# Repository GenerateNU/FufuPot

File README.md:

# Fufu Pot
TODO: Add Blurb

## Directory Structure:
```
.
|
|───production  # contains files needed for final prototype
|   |
|   |───fufpot-eCAD    # contains the KiCAD project
|   └───fufupot-src     # contains the code needed for deployment
|
|───testing     # contains files relevant to testing components
|
└───README.md   # this file!
```

## Practice Good Git Hygiene!
1. Only commit files you intended to change
2. Create branches for each feature, and larger branches for each development effort (i.e. ```develop/*```)
3. Check your branch before starting work
4. Pull frequently to avoid conflicts
5. Make Pull Requests when you are ready to merge into a larger branch

## Git Resources

* [Setting up Git](https://fanatical-colossus-434.notion.site/Git-Installation-and-Setup-d07b7d1ab5544424876f9fd3b4a0b312)
* [Intro to Git Crash Course](https://fanatical-colossus-434.notion.site/Crash-Course-Intro-to-Git-809641611da9478b8f9cca8fd97e49fe)

## EE Resources

* [Intro to KiCAD](https://fanatical-colossus-434.notion.site/EE-Crashcourse-Using-Kicad-To-Design-Schematics-8c7091b07237425bae66616ad1f77371)
* [EE Crash Course](https://fanatical-colossus-434.notion.site/EE-Crash-Course-Hardware-2023-c0c7cd5b55cf401e87f8b6c2c8c84336)

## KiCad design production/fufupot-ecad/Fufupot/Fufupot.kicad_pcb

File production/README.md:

# Production
This directory is for code/schematics/layouts that will be implemented in the final prototype.

> **_NOTE:_** If you have code to test out a component/subsystem, it should probably go into ```/testing```

## Directory Structure:
```
.
|───fufupot-ecad    # contains any schematic/board development files
|
└───fufupot-src     # contains any embedded code or important scripts
```

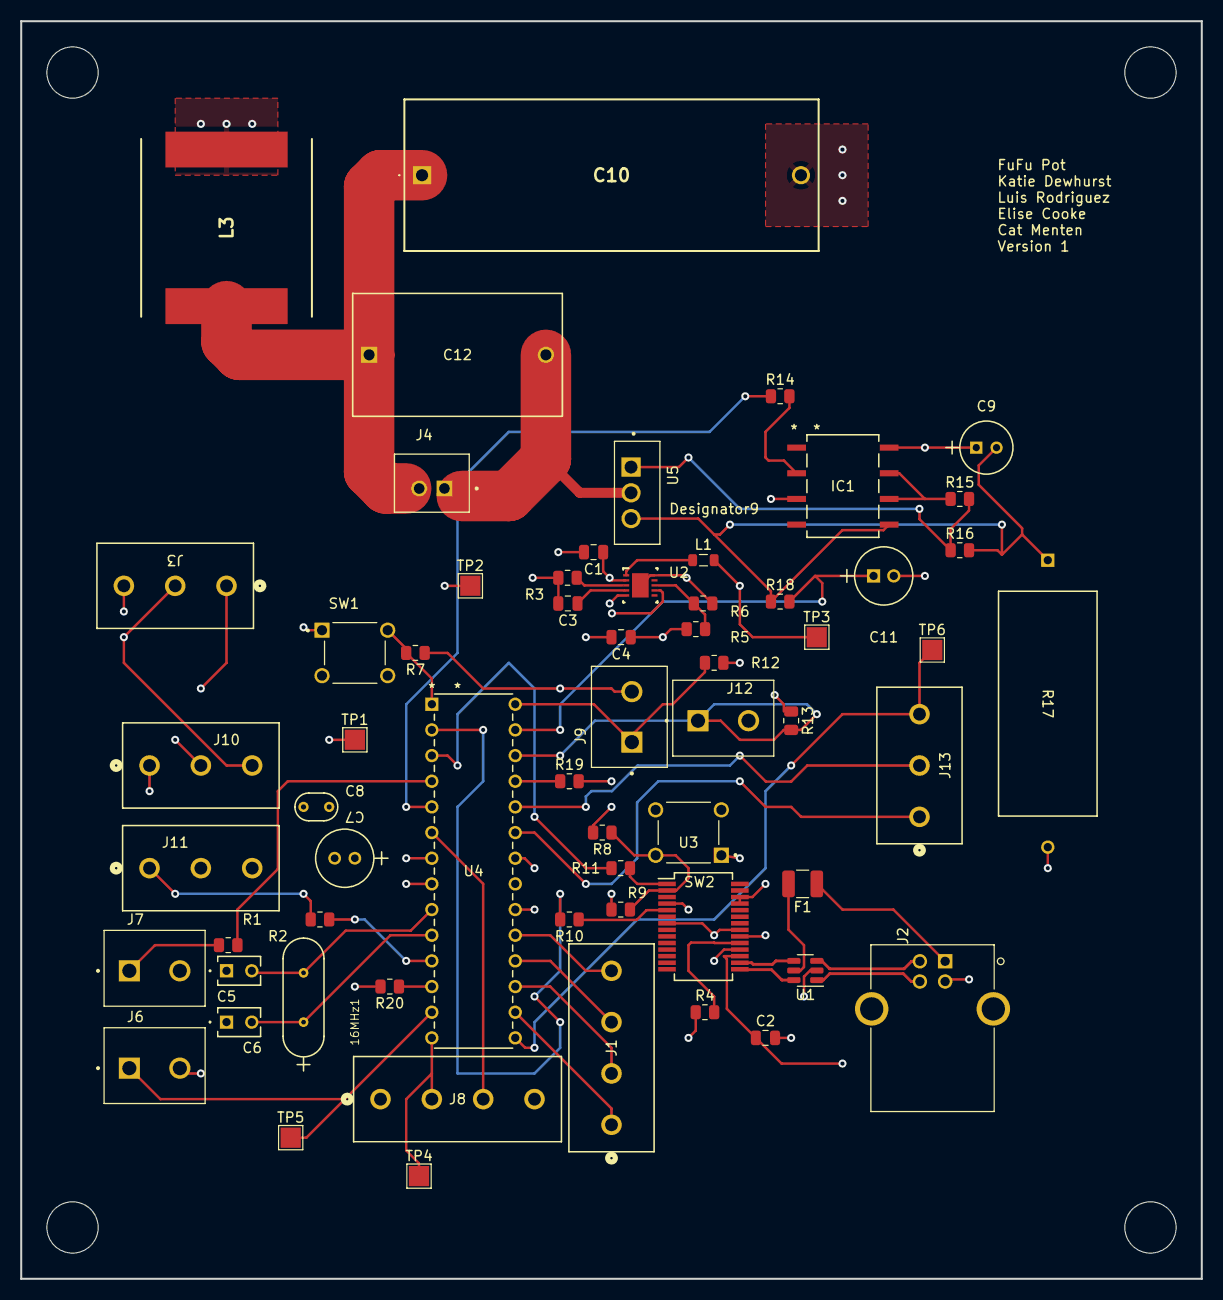
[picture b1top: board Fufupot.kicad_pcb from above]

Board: 4 copper layers, 116.8 x 124.5 mm, 62 parts (0 on the bottom side), 50 nets.

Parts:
16MHz1: Crystal; XTAL_ABL-16_ABR
C1: 1uF; C_0805_2012Metric
C2: 100n; C_0805_2012Metric
C3: 33nF; C_0805_2012Metric
C4: 10uF; C_0805_2012Metric
C5, C6: 22pF; CAP_K-SERIES_15-L2_VIS
C7: 10uF; CAP_YX_5X11_RUB
C8: 0.1 uF; CAP_Y5VE5TL2_VIS
C9: 10uF 25V; U1-E_NCH
C10: 3.3 uF 275V; ECQUAAF335LD
C11: 0.1uF 63V; CAP_WCAP-ATG5_05.0X11.0_WRE
C12: 0.37uF 1200V; CAP_ECWFL_STRAIGHT_20.5LX11.9TX18.5H_PAN
F1: 500mA; Fuse_1210_3225Metric
IC1: FOD3150; SMD8_9P91X6P86_ONS
J1, J8: Conn_01x04; 282837-4_TYC
J2: USB_B; CUI_UJ2-BH-W1-TH
J3, J10, J11, J13: Conn_01x03; 282837-3_TYC
J4: Conn_01x02; JST_B2B-XH-A_LF__SN_
J6, J7, J9, J12: Conn_01x02; HANDSON_KF301-2P
L1: 47uH; L_0805_2012Metric
L3: 10uH; INDPM176169X700N
R1: 200; R_0805_2012Metric
R2, R14: 330; R_0805_2012Metric
R3: 100kOhm; R_0805_2012Metric
R4, R12, R13, R16: 10k; R_0805_2012Metric
R5: 820kOhm; R_0805_2012Metric
R6: 68kOhm; R_0805_2012Metric
R7, R8, R9, R10, R11: 1k; R_0805_2012Metric
R15: 16; R_0805_2012Metric
R17: 0.1 5W; RES_SQP500_22X9P5_YAG
R18: 3.3k; R_0805_2012Metric
R19, R20: 0; R_0805_2012Metric
SW1, SW2: SW_Push; SW_TS02-66-50-BK-100-SCR-D
TP1, TP2, TP3, TP4, TP5, TP6: TestPoint; TestPoint_Pad_2.0x2.0mm
U1: USBLC6-2SC6; SOT-23-6
U2: LM5165DRC; DRC0010J
U3: FT232RL; SSOP-28_5.3x10.2mm_P0.65mm
U4: ATMEGA328P-PN; 28P3_ATM
U5: STGP8NC60KD; TO225P1040X460X1968-3

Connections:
+3V3: C2.1, U3.17 (3V3OUT)
+5V: C7.1, C8.1, J3.1, J9.2, J10.2, J11.2, J12.2, R4.1, R7.1, R8.2, TP1.1, U3.4 (VCCIO), U3.20 (VCC), U4.7 (VCC), U4.20 (AVCC)
+16V: C4.1, C9.1, IC1.8 (VDD), L1.2, R5.1, TP3.1
+48V: C1.1, J3.2, J10.3, L3.1, TP2.1, U2.2 (VIN), U2.7 (EN)
A1: C11.1, R18.2, U4.27 (PC4)
A2: J9.1, R12.2, U4.28 (PC5)
A3: J12.1, R13.2, U4.26 (PC3)
A4: J13.1, U4.23 (PC0)
A5: J13.2, U4.24 (PC1)
D9: R14.1, U4.5 (PD3)
DTR: R8.1, R9.2, SW2.2, U3.2 (DTR)
D_Buzz: J6.1, TP5.1, U4.13 (PD7)
D_LED: R1.1, U4.4 (PD2)
D_LEDStrip: R2.1, U4.11 (PD5)
D_Red: J8.3, U4.6 (PD4)
D_Switch: J8.2, TP4.1, U4.14 (PB0)
GND: C1.2, C2.2, C3.2, C4.2, C5.1, C6.1, C7.2, C8.2, C10.2, C11.2, IC1.3 (CATHODE), J2.4 (GND), J3.3, J6.2, J7.2, J8.1, J8.4, J10.1, J11.3, R3.2, R6.2, R9.1, R12.1, R13.1, R17.2, R19.2, R20.2, SW1.1, SW2.1, U1.2 (GND), U2.5 (RT), U2.10 (GND), U2.11 (PAD), U3.7 (GND), U3.18 (GND), U3.21 (GND), U3.25 (AGND), U3.26 (TEST), U4.8 (GND), U4.22 (GND)
MISO: J1.3, U4.18 (PB4)
MOSI: J1.2, U4.17 (PB3)
unnamed: IC1.2 (ANODE), R14.2
unnamed: IC1.6 (VO1), IC1.7 (VO2), R15.1
unnamed: C9.2, IC1.5 (VSS), R16.2, R17.1, R18.1, U5.3 (E)
unnamed: F1.1, J2.1 (VBUS)
unnamed: C12.2, J4.1, U5.2 (C)
unnamed: C10.1, C12.1, J4.2, L3.2
unnamed: J7.1, R1.2
unnamed: J11.1, R2.2
unnamed: R5.2, R6.1, U2.8 (FB)
unnamed: R3.1, U2.3 (ILIM)
unnamed: C3.1, U2.4 (SS)
unnamed: L1.1, U2.1 (SW)
unnamed: R10.1, U3.5 (RXD)
unnamed: R11.1, U3.1 (TXD)
unnamed: R4.2, U3.19 (~RESET)
unnamed: 16MHz1.2, C5.2, U4.9 (PB6)
unnamed: 16MHz1.1, C6.2, U4.10 (PB7)
unnamed: R19.1, U4.25 (PC2)
unnamed: R20.1, U4.12 (PD6)
unnamed: R15.2, R16.1, U5.1 (G)
PWM Speed Control: J13.3, TP6.1, U4.15 (PB1)
RESET: R7.2, SW1.2, U4.1 (PC6)
RX: R10.2, U4.2 (PD0)
SCK: J1.4, U4.19 (PB5)
SS: J1.1, U4.16 (PB2)
TX: R11.2, U4.3 (PD1)
USB_CON_D+: J2.3 (D+), U1.1 (I/O1)
USB_CON_D-: J2.2 (D-), U1.3 (I/O2)
USB_D+: U1.6 (I/O1), U3.15 (USBD+)
USB_D-: U1.4 (I/O2), U3.16 (USBD-)
VBUS: F1.2, U1.5 (VBUS)

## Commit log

2023-10-01 Made KiCAD Project
    hooray
2023-10-01 Adding random 3v3 net in the bottom right corner of schematic
2023-10-01 haha buffer
    this is a test please don't shoot me in the head
2023-10-02 nick can't see
    eeee
2023-10-02 Deleted Test
    yea
2023-10-02 Test modify code folder
    .
2023-10-02 Made hierarchical schematic sheets
    Now everyone can make their changes on separate schematic sheets and no one will have conflicts <3
2023-10-06 Power Source
    Andy told me to make a simple connector that that shows the 5V and 48V output.
2023-10-12 Heating Schematic Finished
    heating schematic finished
2023-10-12 Update HeatingCircuit.kicad_sch
    Added temp sensing
2023-10-12 Update HeatingCircuit.kicad_sch
    Heating and temp sensing fixed
2023-10-15 Added on to MCU outputs and added motor controller outputs
2023-10-15 Buck Schematic
    First version of my buck schematic
2023-10-16 UI without button
    UI schematic without the button
2023-10-16 Input and Output
    Created labels that represent the input 48V from source and where the output 15V should be.
2023-10-16 UI with Button
    Added the button circuit
2023-10-23 Andy's Updates
    Updating from Andy's recommendation and added UART USB bridge for micro-usb code uploiad
2023-10-24 Exist
    pls don't dissapear again hahahah
2023-10-25 One Page
    compiled all edits into one page
2023-10-26 Labels
    Added GUI labels
2023-10-26 Last minute changes
    Commit with the most recent changes
2023-10-28 Updated Buck Converter
    Modified buck converter values and reference designators
2023-10-30 finished schem
2023-11-02 beginning pcb
2023-11-07 Updates unfinished
2023-11-07 pcb update
2023-11-07 connectors look pretty
2023-11-09 Power Symbol and footprints
    Made +16V power symbol and added footprints.
2023-11-09 Footprints pt2
    Tried adding footprints again
2023-11-09 added footprints to components
2023-11-09 Kicad updates yay
2023-11-09 added footprints
    grrrrrr
2023-11-09 Fixed switches
2023-11-10 Updating USB
2023-11-13 pcb layout
2023-11-13 Fixed GND issues
2023-11-13 pcb first design
2023-11-13 added components
2023-11-13 Fixed power planes
2023-11-13 Fixed ground layer
2023-11-13 fixed gnd of usb
2023-11-13 fixed gnd of usb on pcb
2023-11-13 make pcb more compact
2023-11-14 Changed pcb mounts
2023-11-16 Final Draft, Need to be checked by Andy
2023-11-16 Actual Final Draft- No errors
2023-11-16 i hope it works! fixing routing
2023-11-16 fixed routing
2023-11-17 Added Mounting Holes
2023-11-20 Fix some errors
2023-11-20 Everything Fixed
2023-11-20 Version 3
2023-11-20 Added testpoints
2023-12-08 Adding 3D models
2023-12-08 showcase code that was being shared in a google doc lo
